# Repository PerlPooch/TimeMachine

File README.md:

# Time Machine

Please see the [Project Website](https://home.marcspencer.com/time-machine/) for detailed information, full API, and build details. 

Time Machine brings the past, present, and future to life as a set of three clocks in red, green,
and yellow. Gloriously oversized, each clock uses 0.8-inch LED displays in a case roughly 14 inches
wide. What began as a hallway joke has become a collaborative hardware and software project, with a
small batch planned for friends at the cost of parts.

Each custom circuit board combines an ESP32-C6 controller with three 16-segment alphanumeric
displays for the month and ten seven-segment displays for the day, year, and time. Across a complete
set, that adds up to 39 displays and 354 individually controllable character segments—no Hollywood
magic required. A dedicated LED driver controls brightness, a small OLED provides status, and serial
links connect the clocks.

The Arduino-based firmware provides NTP time synchronization, timezone and daylight-saving support,
and optional OpenWeather integration. An HTTP API controls configuration, text, and built-in
animations, allowing the clocks to display much more than dates and times. The clocks can work
independently or together, and the MPL-2.0 open-source firmware welcomes contributions, experiments,
and new ideas.

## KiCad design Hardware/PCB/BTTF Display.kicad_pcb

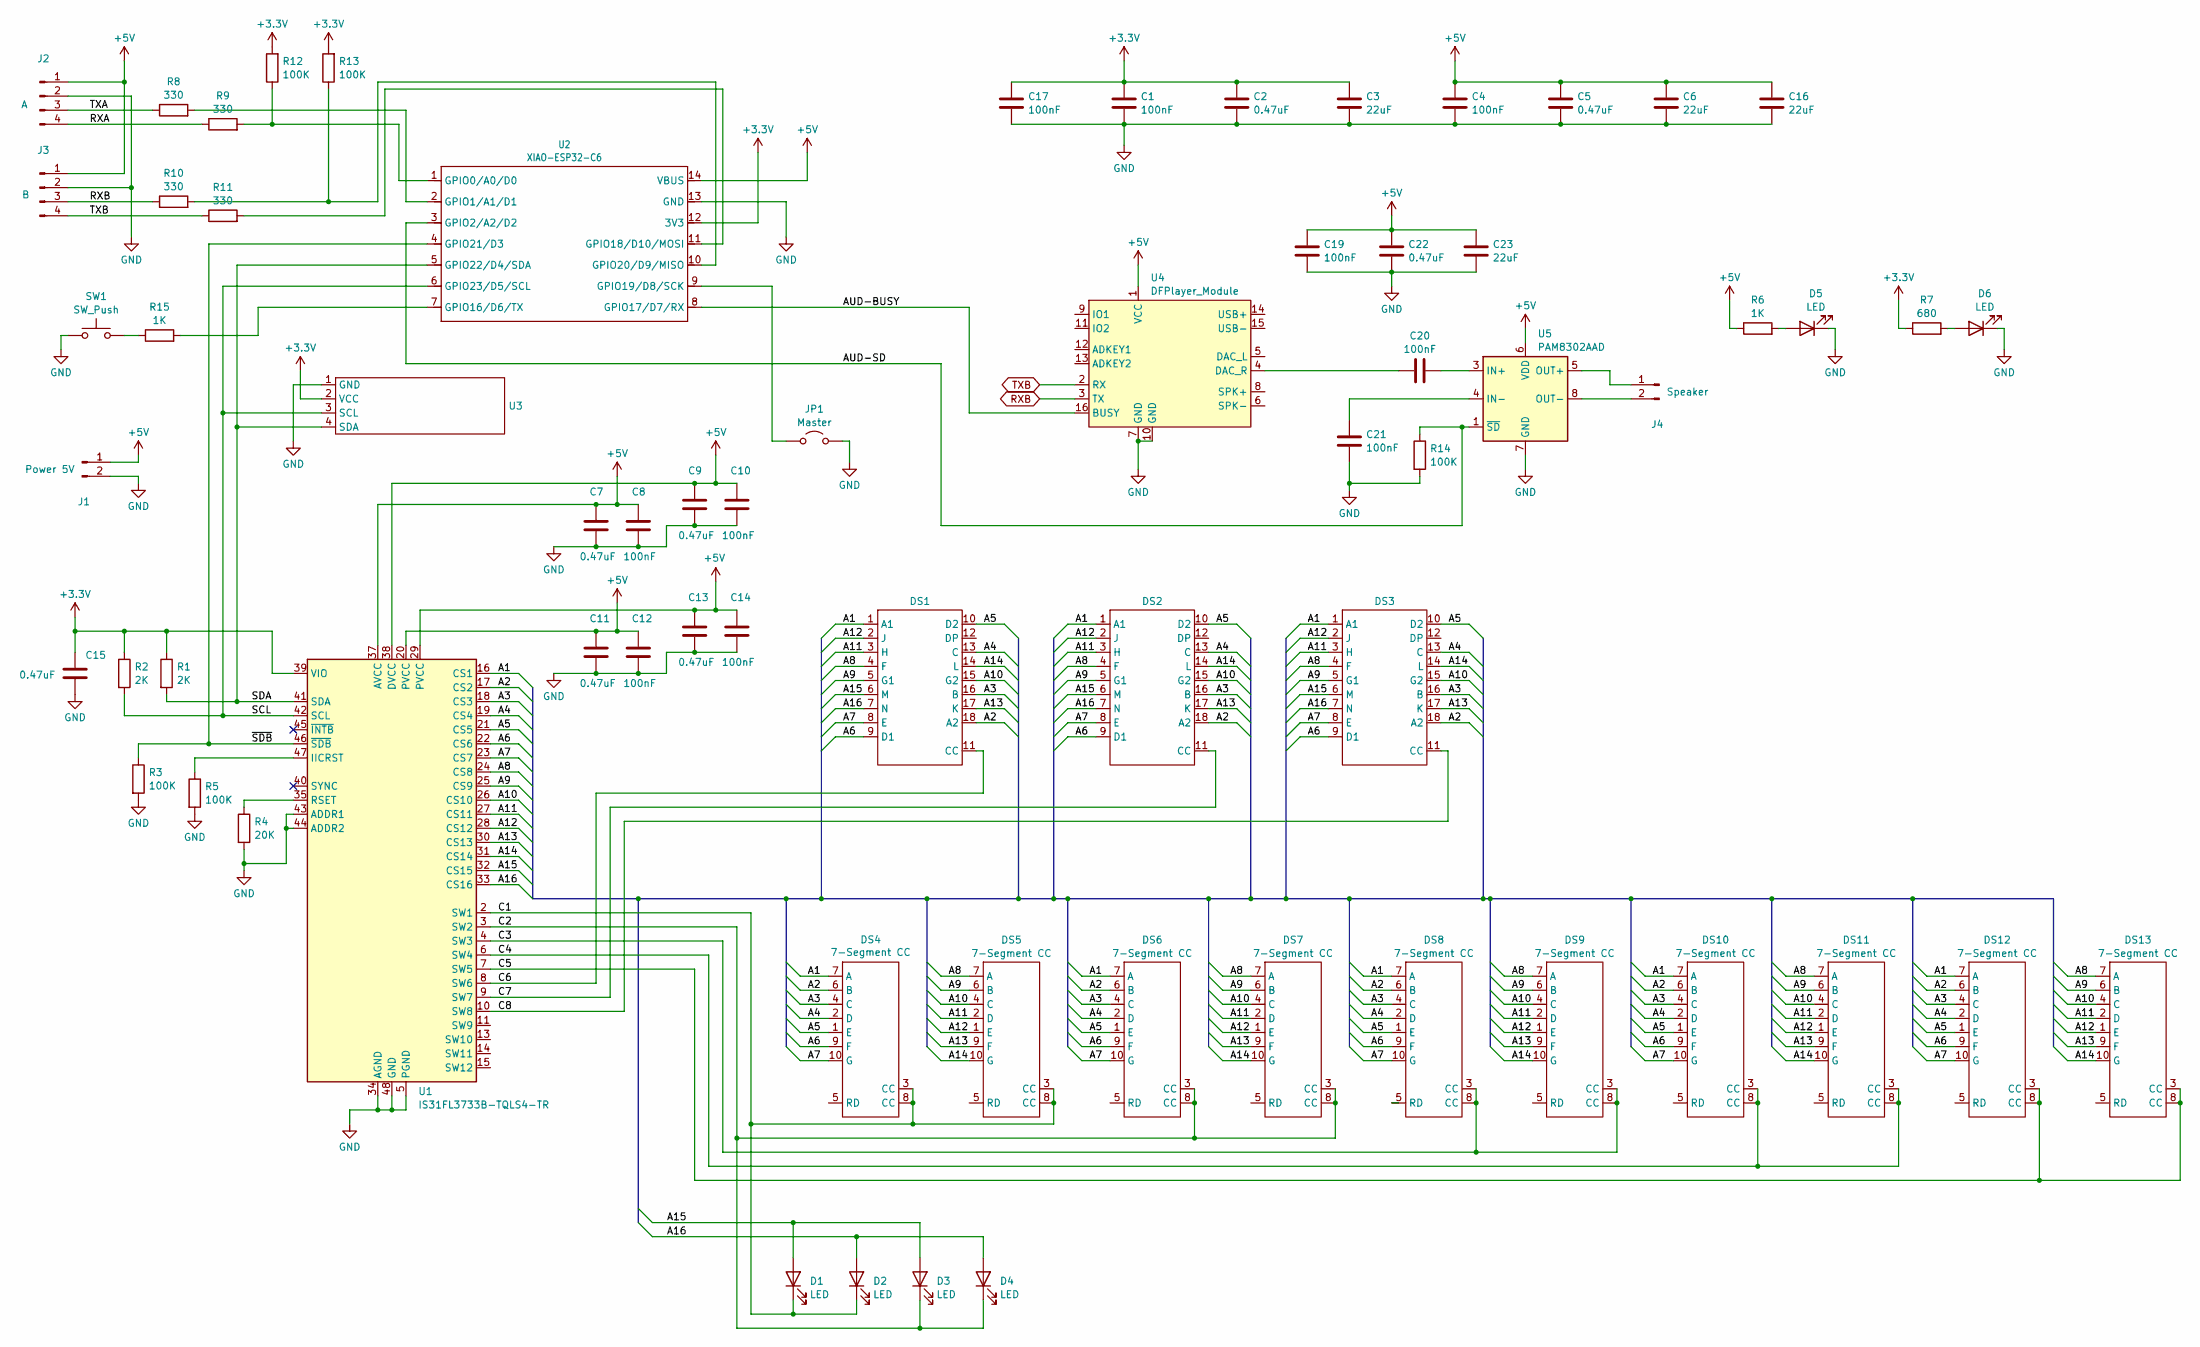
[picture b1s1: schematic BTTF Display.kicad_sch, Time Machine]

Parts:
C1, C4, C8, C10, C12, C14, C17, C19, C20, C21: 100nF; C_0603_1608Metric_Pad1.08x0.95mm_HandSolder
C2, C5, C7, C9, C11, C13, C15, C22: 0.47uF; C_0603_1608Metric_Pad1.08x0.95mm_HandSolder
C3, C6, C16, C23: 22uF; C_1210_3225Metric_Pad1.33x2.70mm_HandSolder
D1, D2, D3, D4: LED; LED_D5.0mm
D5, D6: LED; LED_1206_3216Metric_Pad1.42x1.75mm_HandSolder
DS1, DS2, DS3: LED Display 16-Segment 0.8in
DS4, DS5, DS6, DS7, DS8, DS9, DS10, DS11, DS12, DS13: 7-Segment CC; LED Display 7-Segment 0.8in 10-pin
J1: Power 5V; Connector SIP-2-Soldertail-R
J2: A; Connector SIP-4-Soldertail-L
J3: B; Connector SIP-4-Soldertail-L
J4: Speaker; Connector SIP-2-Soldertail-R
JP1: Master; SolderJumper-2_P1.3mm_Open_RoundedPad1.0x1.5mm
R1, R2: 2K; R_0603_1608Metric_Pad0.98x0.95mm_HandSolder
R3, R5, R12, R13, R14: 100K; R_0603_1608Metric_Pad0.98x0.95mm_HandSolder
R4: 20K; R_0603_1608Metric_Pad0.98x0.95mm_HandSolder
R6, R15: 1K; R_0603_1608Metric_Pad0.98x0.95mm_HandSolder
R7: 680; R_0603_1608Metric_Pad0.98x0.95mm_HandSolder
R8, R9, R10, R11: 330; R_0603_1608Metric_Pad0.98x0.95mm_HandSolder
SW1: SW_Push; SW_PUSH_6mm_H4.3mm
U1: IS31FL3733B-TQLS4-TR; TQFP-48-1EP_7x7mm_P0.5mm_EP5x5mm
U2: XIAO-ESP32-C6; XIAO-ESP32C6-DIP
U3: SSD1306-128x32_Borderless
U4: DFPlayer_Module; DFPlayer
U5: PAM8302AAD; Diodes_SO-8EP

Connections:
+3.3V: C1.1, C2.1, C3.1, C15.1, C17.1, R1.1, R2.1, R7.1, R12.2, R13.2, U1.39 (VIO), U2.12 (3V3), U3.2 (VCC)
+5V: C4.1, C5.1, C6.1, C7.1, C8.1, C9.1, C10.1, C11.1, C12.1, C13.1, C14.1, C16.1, C19.1, C22.1, C23.1, J1.1, J2.1, J3.1, R6.1, U1.20 (PVCC), U1.29 (PVCC), U1.37 (AVCC), U1.38 (DVCC), U2.14 (VBUS), U4.1 (VCC), U5.6 (VDD)
/A1: DS1.1 (A1), DS2.1 (A1), DS3.1 (A1), DS4.7 (A), DS6.7 (A), DS8.7 (A), DS10.7 (A), DS12.7 (A), U1.16 (CS1)
/A2: DS1.18 (A2), DS2.18 (A2), DS3.18 (A2), DS4.6 (B), DS6.6 (B), DS8.6 (B), DS10.6 (B), DS12.6 (B), U1.17 (CS2)
/A3: DS1.16 (B), DS2.16 (B), DS3.16 (B), DS4.4 (C), DS6.4 (C), DS8.4 (C), DS10.4 (C), DS12.4 (C), U1.18 (CS3)
/A4: DS1.13 (C), DS2.13 (C), DS3.13 (C), DS4.2 (D), DS6.2 (D), DS8.2 (D), DS10.2 (D), DS12.2 (D), U1.19 (CS4)
/A5: DS1.10 (D2), DS2.10 (D2), DS3.10 (D2), DS4.1 (E), DS6.1 (E), DS8.1 (E), DS10.1 (E), DS12.1 (E), U1.21 (CS5)
/A6: DS1.9 (D1), DS2.9 (D1), DS3.9 (D1), DS4.9 (F), DS6.9 (F), DS8.9 (F), DS10.9 (F), DS12.9 (F), U1.22 (CS6)
/A7: DS1.8 (E), DS2.8 (E), DS3.8 (E), DS4.10 (G), DS6.10 (G), DS8.10 (G), DS10.10 (G), DS12.10 (G), U1.23 (CS7)
/A8: DS1.4 (F), DS2.4 (F), DS3.4 (F), DS5.7 (A), DS7.7 (A), DS9.7 (A), DS11.7 (A), DS13.7 (A), U1.24 (CS8)
/A9: DS1.5 (G1), DS2.5 (G1), DS3.5 (G1), DS5.6 (B), DS7.6 (B), DS9.6 (B), DS11.6 (B), DS13.6 (B), U1.25 (CS9)
/A10: DS1.15 (G2), DS2.15 (G2), DS3.15 (G2), DS5.4 (C), DS7.4 (C), DS9.4 (C), DS11.4 (C), DS13.4 (C), U1.26 (CS10)
/A11: DS1.3 (H), DS2.3 (H), DS3.3 (H), DS5.2 (D), DS7.2 (D), DS9.2 (D), DS11.2 (D), DS13.2 (D), U1.27 (CS11)
/A12: DS1.2 (J), DS2.2 (J), DS3.2 (J), DS5.1 (E), DS7.1 (E), DS9.1 (E), DS11.1 (E), DS13.1 (E), U1.28 (CS12)
/A13: DS1.17 (K), DS2.17 (K), DS3.17 (K), DS5.9 (F), DS7.9 (F), DS9.9 (F), DS11.9 (F), DS13.9 (F), U1.30 (CS13)
/A14: DS1.14 (L), DS2.14 (L), DS3.14 (L), DS5.10 (G), DS7.10 (G), DS9.10 (G), DS11.10 (G), DS13.10 (G), U1.31 (CS14)
/A15: D1.2 (A), D3.2 (A), DS1.6 (M), DS2.6 (M), DS3.6 (M), U1.32 (CS15)
/A16: D2.2 (A), D4.2 (A), DS1.7 (N), DS2.7 (N), DS3.7 (N), U1.33 (CS16)
/AUD-BUSY: U2.8 (GPIO17/D7/RX), U4.16 (BUSY)
/AUD-SD: R14.1, U2.3 (GPIO2/A2/D2), U5.1 (~SD)
/C1: D1.1 (K), D2.1 (K), DS4.3 (CC), DS4.8 (CC), DS5.3 (CC), DS5.8 (CC), U1.2 (SW1)
/C2: D3.1 (K), D4.1 (K), DS6.3 (CC), DS6.8 (CC), DS7.3 (CC), DS7.8 (CC), U1.3 (SW2)
/C3: DS8.3 (CC), DS8.8 (CC), DS9.3 (CC), DS9.8 (CC), U1.4 (SW3)
/C4: DS10.3 (CC), DS10.8 (CC), DS11.3 (CC), DS11.8 (CC), U1.6 (SW4)
/C5: DS12.3 (CC), DS12.8 (CC), DS13.3 (CC), DS13.8 (CC), U1.7 (SW5)
/C6: DS1.11 (CC), U1.8 (SW6)
/C7: DS2.11 (CC), U1.9 (SW7)
/C8: DS3.11 (CC), U1.10 (SW8)
/RXA: J2.4, R9.1
/SCL: R2.2, U1.42 (SCL), U2.6 (GPIO23/D5/SCL), U3.3 (SCL)
/SDA: R1.2, U1.41 (SDA), U2.5 (GPIO22/D4/SDA), U3.4 (SDA)
/TXA: J2.3, R8.1
/~SDB: R3.1, U1.46 (~SDB), U2.4 (GPIO21/D3)
GND: C1.2, C2.2, C3.2, C4.2, C5.2, C6.2, C7.2, C8.2, C9.2, C10.2, C11.2, C12.2, C13.2, C14.2, C15.2, C16.2, C17.2, C19.2, C21.1, C22.2, C23.2, D5.1 (K), D6.1 (K), J1.2, J2.2, J3.2, JP1.2 (B), R3.2, R4.2, R5.2, R14.2, SW1.1, U1.5 (PGND), U1.12 (PGND), U1.34 (AGND), U1.43 (ADDR1), U1.44 (ADDR2), U1.48 (GND), U1.49 (GND), U2.13 (GND), U3.1 (GND), U4.7 (GND), U4.10 (GND), U5.7 (GND)
unnamed: D5.2 (A), R6.2
unnamed: D6.2 (A), R7.2
unnamed: J4.1, U5.5 (OUT+)
unnamed: J4.2, U5.8 (OUT-)
unnamed: JP1.1 (A), U2.9 (GPIO19/D8/SCK)
unnamed: R15.1, SW1.2
unnamed: R5.1, U1.47 (IICRST)
unnamed: R4.1, U1.35 (RSET)
unnamed: R9.2, R12.1, U2.1 (GPIO0/A0/D0)
unnamed: R8.2, U2.2 (GPIO1/A1/D1)
unnamed: R15.2, U2.7 (GPIO16/D6/TX)
unnamed: R11.2, U2.11 (GPIO18/D10/MOSI)
unnamed: R10.2, R13.1, U2.10 (GPIO20/D9/MISO)
unnamed: C20.1, U4.4 (DAC_R)
unnamed: C20.2, U5.3 (IN+)
unnamed: C21.2, U5.4 (IN-)
RXB: J3.3, R10.1, U4.3 (TX)
TXB: J3.4, R11.1, U4.2 (RX)

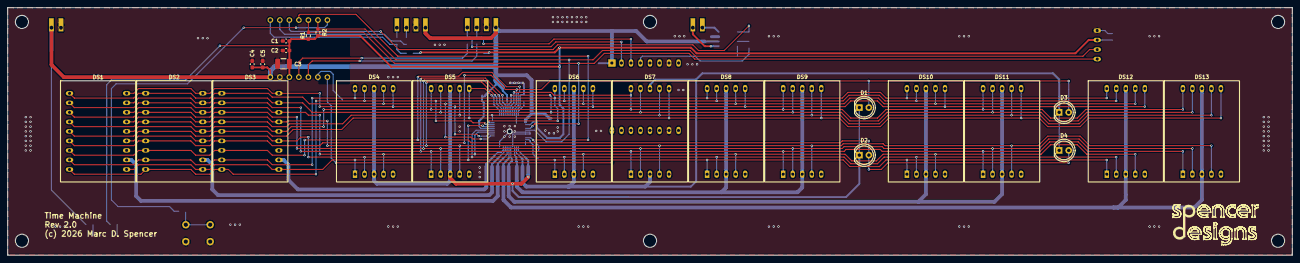
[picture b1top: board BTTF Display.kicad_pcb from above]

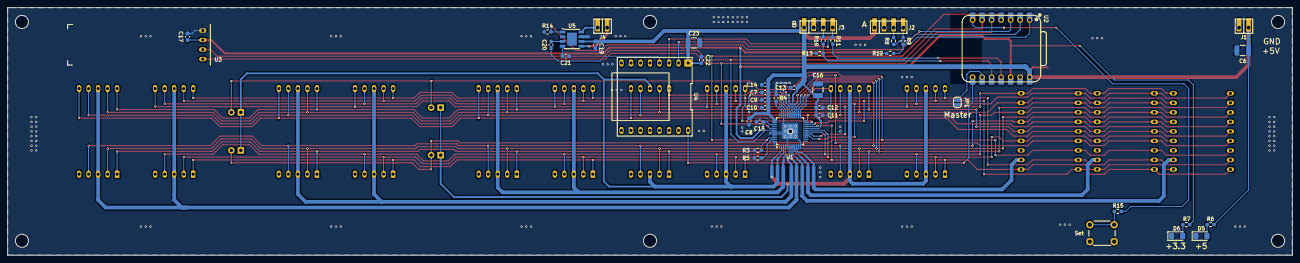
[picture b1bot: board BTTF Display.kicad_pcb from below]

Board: 2 copper layers, 342.9 x 66.0 mm, 67 parts (43 on the bottom side), 52 nets.

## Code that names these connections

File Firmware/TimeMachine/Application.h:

/*
 * ===========================================================================
 * File:      TimeMachine/Application.h
 * Firmware:  0.5.1
 * Git base:  1e4e91f4dbce
 *
 * Copyright (c) 2026 Marc D. Spencer.
 * All Rights Reserved under the applicable license.
 * SPDX-License-Identifier: MPL-2.0
 *
 * This Source Code Form is subject to the terms of the Mozilla Public
 * License, v. 2.0. If a copy of the MPL was not distributed with this
 * file, You can obtain one at https://mozilla.org/MPL/2.0/.
 * ===========================================================================
 */

#pragma once

#include <HardwareSerial.h>
#include "SerialProtocol.h"
#include <MDS_Config.h>
#include <MDS_WiFi.h>
#include <MDS_HTTP.h>
#include <MDS_Time.h>
#include <MDS_Weather.h>
#include "ApplicationApi.h"
#include "TimeController.h"
#include "WeatherController.h"
#include "Clock.h"
#include "Tests.h"
#include "Display.h"
#include "Button.h"

class MDS_Display;

// Own application services and modes; borrow hardware constructed by the sketch.
class Application {
public:
	enum class Mode {
		Tests,
		Clock
	};

	// Lifecycle is separate from the selected display mode and hardware capabilities.
	enum class State : uint8_t {
		Uninitialized,
		Starting,
		SegmentTest,
		Running,
		DisplayFault,
		ConfigFault,
		ResetHeld,
		Resetting,
		ResetFailed,
		Rebooting
	};

	Application(Mode mode, MatrixDriver& matrix, MDS_Display& oled, Button& button);
	Application(const Application&) = delete;
	Application& operator=(const Application&) = delete;

	// Hardware readiness comes from the harness; services can run without a display.
	// The jumper supplies defaultPrimary; saved configuration overrides that default.
	// Success starts the asynchronous lamp test; the selected mode begins afterward.
	bool begin(const char* version, bool defaultPrimary, bool busReady, bool oledReady);
	void tick();

	// Report the current lifecycle state without advancing application work.
	State state() const { return state_; }

private:
	void transitionTo(State next);
	static const char* stateName(State state);
	bool beginConfig(const char* version, bool defaultPrimary);
	bool beginMode();
	void serviceHttp();
	void serviceSerial();
	void serviceIPAddresses(uint32_t now);
	bool receiveIPAddress(const char* address, size_t length, size_t index);
	void queueWiFiCredentials(uint32_t now);
	void receiveWiFiCredentials(const uint8_t* payload, size_t length, const char* portName);
	bool routeDisplayCommand(const Display::DisplayCommand& command);
	bool routeSerialPayload(uint8_t destinations, const char* payload, size_t length);
	void receiveSerial(HardwareSerial& port, SerialProtocol::Receiver& receiver, size_t index, const char* name);
	void serviceButton();
	void showReset();
	void factoryReset();

	const Mode mode_;
	MatrixDriver& matrix_;
	MDS_Display& oled_;
	Button& button_;
	static constexpr uint32_t ResetHoldMs = 5000;
	State state_ = State::Uninitialized;
	State resumeState_ = State::DisplayFault; // Destination after reset-button release.
	uint32_t resetPressedAt_ = 0;
	Display::Frame resetFrame_; // Output to restore if the reset is canceled.
	bool oledReady_ = false;

	// Port A / J2: RX GPIO0, TX GPIO1; USB CDC remains the debug console.
	HardwareSerial serialA_{1};
	// Port B / J3 uses UART0 on RX GPIO20 and TX GPIO18.
	HardwareSerial serialB_{0};
	struct SerialTransmit {
		uint8_t frame[SerialProtocol::BufferBytes] = {};
		size_t length = 0;
		size_t sent = 0;
		bool credentials = false;
		bool ipAddress = false;
	};
	SerialTransmit serialTransmit_[2];
	struct SerialResponse {
		SerialProtocol::Status status = SerialProtocol::Status::Ok;
		size_t sent = 0;
		bool pending = false;
	};
	SerialResponse serialResponse_[2];
	SerialProtocol::Receiver receiverA_;
	SerialProtocol::Receiver receiverB_;
	static constexpr uint32_t PingIntervalMs = 1000;
	uint32_t lastPingAt_[2] = {};
	static constexpr uint32_t WiFiBroadcastIntervalMs = 10000;
	uint32_t lastWiFiAt_[2] = {};
	bool primaryActive_ = false;
	static constexpr uint32_t IPAnnouncementIntervalMs = 10000;
	static constexpr uint32_t PeerIPExpiryMs = 30000;
	char localIPAddress_[16] = {};
	bool ipAnnouncementDue_[2] = {};
	uint32_t lastIPAt_[2] = {};
	uint32_t peerIPAt_[2] = {};
	bool peerIPKnown_[2] = {};

	Display display_;
	static constexpr const char* ConfigPath = "/config.json";
	MDS_Config config_{ConfigPath};
	MDS_WiFi wifi_;
	MDS_HTTP http_;
	MDS_Time time_;
	MDS_Weather weather_;
	ApplicationApi api_;
	TimeController timeController_;
	WeatherController weatherController_;
	Clock clock_;
	Tests tests_;
};
